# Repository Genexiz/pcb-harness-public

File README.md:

# PCB Harness

Standalone KiCad-grounded PCB design harness under development. M0 and the initial M1 scratch Kernel are verified on KiCad 10.0.6. This is not an autonomous PCB designer yet.

This project is intended for **open-source release** under Apache-2.0 (`LICENSE`); third-party files keep their own licenses. See [open-source preparation](docs/open-source.md) and [third-party notices](THIRD_PARTY.md).

Design: [Roadmap](PCB%20Harness%20%E2%80%94%20Development%20Roadmap.md)

## Run the current checks

Requires Python 3.11+ and KiCad on macOS. Original M0 baseline is 10.0.0; current CLI regression is verified on 10.0.6. Paths in this probe intentionally match the installed macOS bundle; portable discovery belongs to the Kernel milestone.

```sh
python3 -m venv .venv
.venv/bin/python -m pip install -r requirements-mcp.lock
.venv/bin/python -m pip install -e '.[test,mcp]' --no-deps --no-build-isolation
.venv/bin/python experiments/kicad-ipc/verify_fixture.py
.venv/bin/python -m pytest -q
```

`verify_fixture.py` runs real DRC with schematic parity, ERC, and SVG export on the committed three-resistor fixture. It writes raw JSON, command/stdout/stderr evidence, hashes and a summary to `runs/capability/cli/`. Runs are ignored by Git; source fixtures and tests are retained.

The scratch circuit uses three parallel passive resistors with two nets. `Harness:Probe_R` is a custom geometric probe footprint, **not a production resistor package**. No part facts or fabrication readiness are implied by this test circuit.

Full tests include known-bad board copies for shorts, clearance, track width, open connections, schematic/PCB mismatches and output pin conflicts. The report reader rejects missing/unknown schemas, missing sections, omitted severities, source mismatch, malformed reports and failed CLI execution. A pre-existing report cannot turn a failed command into pass.

The native custom rule is independently tested with its global width floor lowered. Thresholds use explicit `mm`. KiCad 10.0.0 CLI can silently ignore malformed rule text, so the M0 IPC wrapper still accepts only the exact tested scratch-rule subset. M3 adds a separate saved-file fabrication compiler with native negative tests; it does not relax that IPC guard.

On this Codex sandbox, KiCad `--schematic-parity` requires an approved command outside the sandbox: macOS GUI initialization otherwise aborts the CLI. Run normally from a local terminal, or use the tool's approved execution path. Do not interpret the abort/missing report as a board result.

## IPC probe

1. Run `.venv/bin/python experiments/kicad-ipc/prepare_live_fixture.py` once, then open `runs/capability/live/board.kicad_pcb` in a **separate PCB Editor window**. The committed fixture remains unchanged. The preparation command refuses to overwrite an existing live project.
2. Enable KiCad API under Preferences → Plugins. This is a local API; no MCP service is published.
3. Run:

```sh
.venv/bin/python experiments/kicad-ipc/probe_ipc.py
```

The probe selects the exact scratch document by resolved project/file path and rejects ambiguous or unrelated documents before modifying anything. The default socket is `ipc:///tmp/kicad/api.sock`; specify `--socket` if the scratch editor uses another socket. Do not choose a socket based only on the fact that it connects.

Probes exercise explicit coordinates, native commits, readback and restoration. They do not invoke an autorouter or SWIG. `native_flip_items` may be unsupported on KiCad 10.0.0: the installed binding 0.8.0 was built against 10.0.6 and capability detection is required per method.

Only run on the scratch fixture, without human edits during mutation probes. The probe is experimental and is not the production multi-writer/checkpoint recovery system. If a rollback cannot restore the baseline, it stops before further mutations.

Multiple KiCad applications can expose different sockets: in the continuation run, `api.sock` belonged to KiCad Manager and rejected `GetOpenDocuments`; PCB Editor used `api-<pid>.sock`. After restarting PCB Editor, discover its new socket and confirm the exact document again. Never retry a mutation just because a connection failed.

`probe_lost_reply.py --socket <confirmed socket> --output <new run directory>` sends one native commit and closes the connection before receiving its reply. It retains the uncertain operation record, reconciles through an independent client and restores only the exact expected scratch state. It does not prove recovery from an OS crash or arbitrary concurrent edits.

`probe_render.py --svg <native SVG> --geometry <IPC baseline.json> --output <new run directory>` validates the M0 fixture's pad centers, copper endpoints and rectangular outline, then creates an R1 crop with an explicit mm viewBox. This calibration is specific to the observed KiCad 10.0.0 fixture output.

Revert guards inspect the complete serialized PCB and related file hashes; conflict/readback failure leaves an explicit uncertain outcome and attempts a recovery copy. Checks cannot eliminate a race with another writer or observe every unsaved project-setting edit, so the single-writer requirement remains in force.

## Board images

MCP now provides whole-board and region PNG tools, with layers, revision and calibrated mm/pixel metadata. Images are returned directly as MCP ImageContent; no model API key is needed. Memory diagrams remain labelled test-only. Native saved-fixture renders and modern/legacy image delivery are verified.

A separate editor-window capture tool is implemented for macOS with explicit instance/window binding and existing Screen Recording permission. Actual live render/capture and host vision analysis are still unverified in the current environment. See [visual tools](docs/mcp.md#visual-tools-14-tools-total) for parameters, setup and current limits.

## Current status

M0's core capability gate is verified: native geometry edits, commit/revert, save/reopen, custom rule negatives, zone fill, saved-board DRC/ERC/parity and fixture SVG calibration. Manual GUI edits and a lost commit reply were also tested. See [capability report](docs/capabilities/kicad-10-macos.md) for exact evidence and remaining recovery limits. The initial M1 Kernel is documented in [Kernel guide](docs/kernel.md); its current native acceptance status is separate from the M0 completion claim.

The primary workflow is **Subscription-driven local MCP**: Codex signed in with ChatGPT calls the MCP tools, which use the same Kernel and local KiCad. Harness will not require a model API key or make its own inference calls in this workflow. The local STDIO MCP server is implemented and SDK/protocol-tested; see [MCP guide](docs/mcp.md). Native mutations/checkpoints require the exact connected scratch backend on verified KiCad 10.0.6; other versions stay gated. M2 single-agent routing feasibility passed 4/5 native runs in `runs/routing/m2-2026-10-09-r3`; see [M2 evidence and limits](docs/capabilities/m2-progress.md). API-key providers are optional future work only when requested.

KiCad API means the local IPC command interface, not an LLM API key. Host subscription access/limits remain separate from Kernel action/time budgets. Host model tokens/costs not exposed to Harness must be marked unavailable. Do not commit credentials or logs containing them.

MCP runs freeze their action/time limits at launch (default 300 admitted write requests and 20 minutes from the first write). Rejected/replayed writes count, reconnect does not reset them, and exhausted runs retain read/verification/image tools. See [run-envelope semantics and recovery limits](docs/mcp.md#frozen-run-envelope). The passing M2 runs used six admitted writes and 232.850–240.979 seconds each. One run stopped on a lost checkpoint reply with `RECOVERY_REQUIRED` and was not retried.

M3 now provides strict requirements/circuit schemas, hash-bound source/parts auditing, independent upstream review, fabrication coverage/rules and readable native schematic/PCB bootstrap. Post-review acceptance passes eight circuit negatives and eight native rule negatives, with clean ERC/geometry/parity and exact exported netlist on the unrouted positive fixture; seven review findings are fixed and 373 tests pass. See [M3 evidence and limits](docs/capabilities/m3-progress.md). Real part/fabrication confirmations remain release blockers; M4 real-target feasibility is next.

M4 now has a real STM32F103C8T6 candidate pin/DMA/EXTI allocation, bounded SPI wire-time and power estimates, source snapshots, and a cross-compiled resource probe with hash-bound ELF/map evidence. Complete interface firmware, power/thermal, mechanical, errata and actual circuit/native gates remain unresolved; layout and release stay closed. See [M4 progress and required evidence](docs/capabilities/m4-progress.md) and [benchmark reproduction](benchmarks/stm32-communications/README.md).

The M4 engineering continuation adds source-bound CAN FIFO/timestamp/bit-timing calculations, separate transceiver VDD/VIO loads, supply-range screening, mechanical conflicts and17 planned errata policies. A [concrete circuit draft](benchmarks/stm32-communications/circuit-draft.md) covers all nine interfaces. Independent review fixes enforce supply-domain applicability, complete candidate inventory and atomic source-byte checks; see [review and limits](docs/capabilities/m4-engineering-review.md). This remains a pre-layout draft; exact support BOM/assets, complete drivers, thermal/module limits and native circuit acceptance are still required.

The [core asset preparation runner](docs/capabilities/m4-core-preparation.md) now freezes original geometry, creates six standalone exact-MPN symbol/footprint candidates and an eight-IC/nine-core-instance BOM, and verifies each derivative against its captured source. Independent review fixes package/document admission and per-part/BOM semantic linkage; 528 tests pass. Pinout/package facts, WIZ550io assets and the complete support BOM remain unresolved; layout stays closed.

The [core pin evidence packet](docs/capabilities/m4-core-pin-evidence.md) now
binds authored manufacturer/symbol aliases to the saved assets and original
publisher revisions:55 pins across five sourced IC types, plus an MCU inventory
whose original PDF is still unavailable. Ten M3 identity facts remain
unconfirmed. Source binding does not approve electrical types, land patterns,
exact-orderable availability or the complete circuit; layout remains closed.
One review finding is fixed; the final regression suite passes561 tests.

The [real-target review schematic](docs/capabilities/m4-circuit-review.md) now
contains104 components and all nine interfaces, with a manufacturer-CAD-derived
WIZ550io candidate. Native endpoint sets match73 nets/19 NC contacts. ERC still
has four errors and exact support/source/firmware/thermal gates remain open;
this candidate is not an accepted PCB or completed M4.

The [integrated M4 checkpoint](docs/capabilities/m4-completion.md) adds a
141-component circuit with zero ERC violations (KiCad default-ignored checks and
three declared supply-drive markers stated) and nine-driver firmware at
34,708 B Flash / 17,160 B RAM. After an independent review and fixes, the sealed
`runs/m4/completion-2026-10-11-r3` reconstructs 9 open pre-layout blockers:
timing, current-limit applicability, socket fit, power/thermal, errata and
USB/protection. All required facts are recorded but unconfirmed. Layout remains closed.

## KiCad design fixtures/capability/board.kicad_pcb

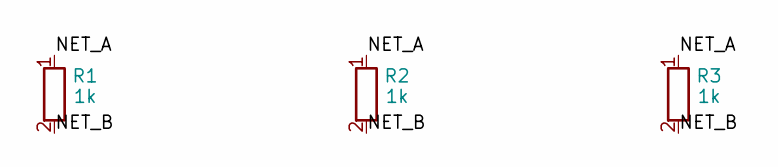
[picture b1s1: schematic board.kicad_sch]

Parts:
R1, R2, R3: 1k; Probe_R

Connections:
/NET_A: R1.1, R2.1, R3.1
/NET_B: R1.2, R2.2, R3.2

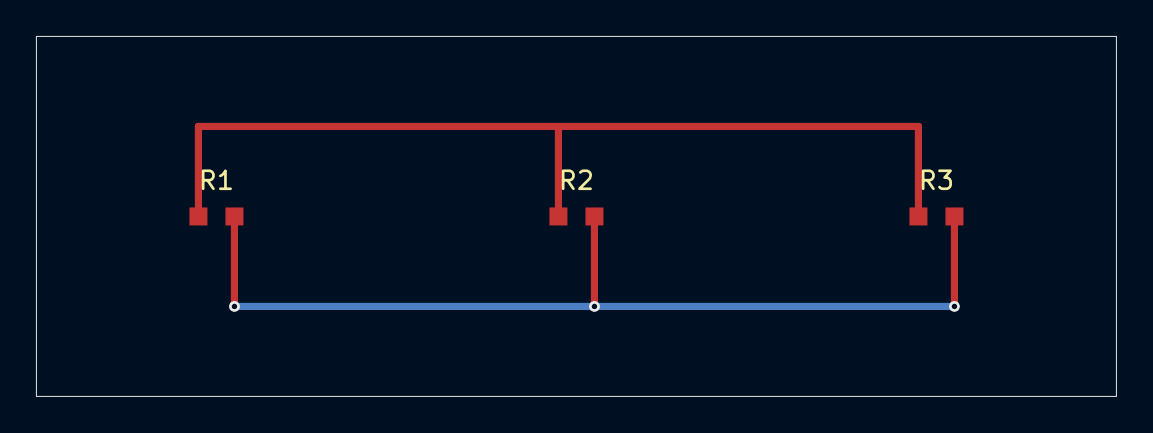
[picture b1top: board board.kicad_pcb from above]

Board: 2 copper layers, 60.0 x 20.0 mm, 3 parts (0 on the bottom side), 2 nets.
